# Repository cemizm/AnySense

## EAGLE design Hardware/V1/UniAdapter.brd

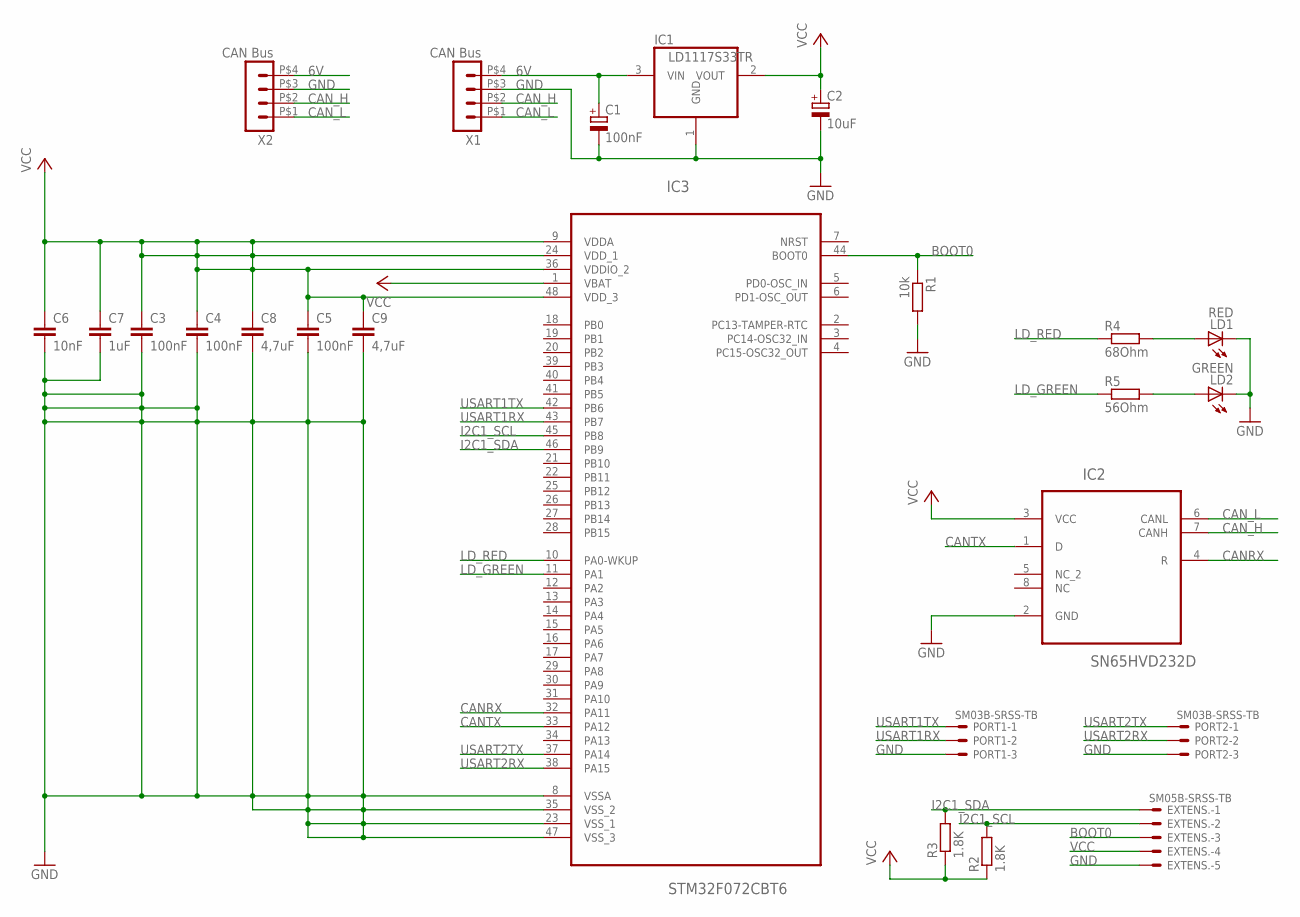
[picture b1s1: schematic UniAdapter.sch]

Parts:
C1: 100nF; CT3216
C2: 10uF; CT3216
C3, C4, C5: 100nF; C0603
C6: 10nF; C0603
C7: 1uF; C0603
C8, C9: 4,7uF; C0603
EXTENS.: SM05B-SRSS-TB
IC1: LD1117S33TR; SOT223
IC2: SN65HVD232D; SOIC127P600X175-8N
IC3: STM32F072CBT6; LQFP48
LD1: RED; CHIPLED_0603
LD2: GREEN; CHIPLED_0603
PORT1, PORT2: SM03B-SRSS-TB
R1: 10k; R0603
R2, R3: 1.8K; R0603
R4: 68Ohm; R0603
R5: 56Ohm; R0603
X1, X2: CAN Bus; 43650-0412

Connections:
6V: C1.+, IC1.3 (VIN), X1.P$4 (4), X2.P$4 (4)
BOOT0: EXTENS..3, IC3.44 (BOOT0), R1.1
CANRX: IC2.4 (R), IC3.32 (PA11)
CANTX: IC2.1 (D), IC3.33 (PA12)
CAN_H: IC2.7 (CANH), X1.P$2 (2), X2.P$2 (2)
CAN_L: IC2.6 (CANL), X1.P$1 (1), X2.P$1 (1)
GND: C1.-, C2.-, C3.2, C4.2, C5.2, C6.2, C7.2, C8.2, C9.2, EXTENS..5, IC1.1 (GND), IC2.2 (GND), IC3.8 (VSSA), IC3.23 (VSS_1), IC3.35 (VSS_2), IC3.47 (VSS_3), LD1.C, LD2.C, PORT1.3, PORT2.3, R1.2, X1.P$3 (3), X2.P$3 (3)
I2C1_SCL: EXTENS..2, IC3.45 (PB8), R2.2
I2C1_SDA: EXTENS..1, IC3.46 (PB9), R3.2
LD_GREEN: IC3.11 (PA1), R5.1
LD_RED: IC3.10 (PA0-WKUP), R4.1
unnamed: LD1.A, R4.2
unnamed: LD2.A, R5.2
USART1RX: IC3.43 (PB7), PORT1.2
USART1TX: IC3.42 (PB6), PORT1.1
USART2RX: IC3.38 (PA15), PORT2.2
USART2TX: IC3.37 (PA14), PORT2.1
VCC: C2.+, C3.1, C4.1, C5.1, C6.1, C7.1, C8.1, C9.1, EXTENS..4, IC1.2 (VOUT), IC2.3 (VCC), IC3.1 (VBAT), IC3.9 (VDDA), IC3.24 (VDD_1), IC3.36 (VDDIO_2), IC3.48 (VDD_3), R2.1, R3.1

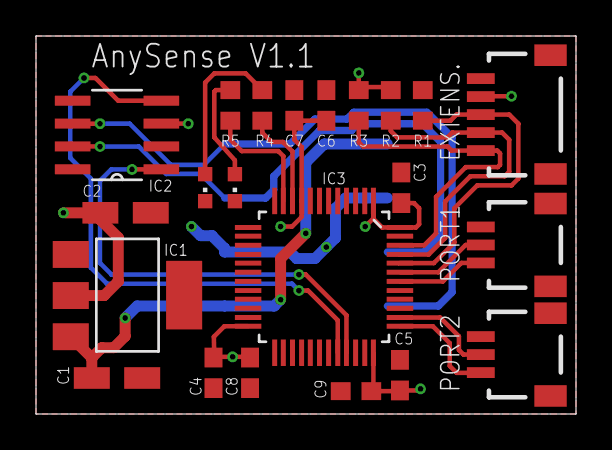
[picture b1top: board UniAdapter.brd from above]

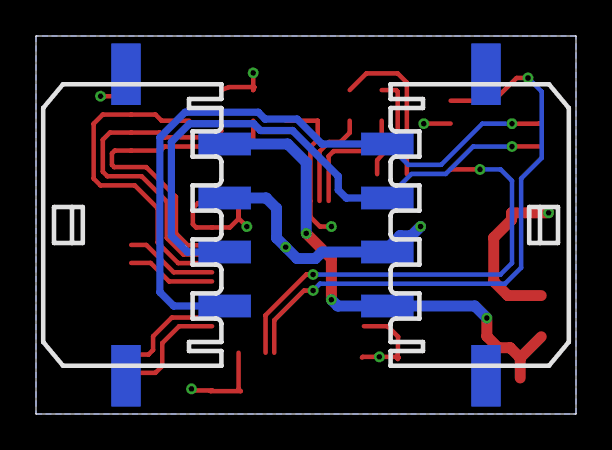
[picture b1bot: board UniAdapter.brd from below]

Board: 2 copper layers, 30.0 x 21.0 mm, 24 parts (2 on the bottom side), 18 nets.

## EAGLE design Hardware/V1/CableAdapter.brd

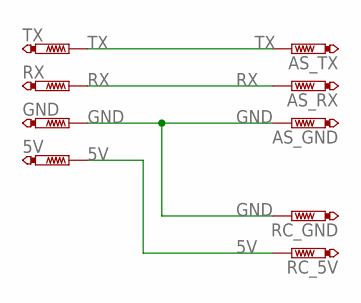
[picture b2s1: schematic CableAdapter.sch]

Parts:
5V: PTR1TP20SQ; TP20SQ
AS_GND: PTR1TP20SQ; TP20SQ
AS_RX: PTR1TP20SQ; TP20SQ
AS_TX: PTR1TP20SQ; TP20SQ
GND: PTR1TP20SQ; TP20SQ
RC_5V: PTR1TP20SQ; TP20SQ
RC_GND: PTR1TP20SQ; TP20SQ
RX: PTR1TP20SQ; TP20SQ
TX: PTR1TP20SQ; TP20SQ

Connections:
5V: 5V.TP, RC_5V.TP
GND: AS_GND.TP, GND.TP, RC_GND.TP
RX: AS_RX.TP, RX.TP
TX: AS_TX.TP, TX.TP

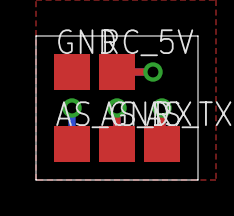
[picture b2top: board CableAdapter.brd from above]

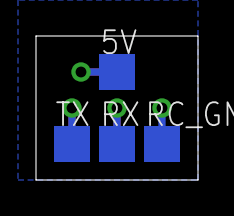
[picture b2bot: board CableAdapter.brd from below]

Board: 2 copper layers, 9.0 x 8.0 mm, 9 parts (4 on the bottom side), 4 nets.

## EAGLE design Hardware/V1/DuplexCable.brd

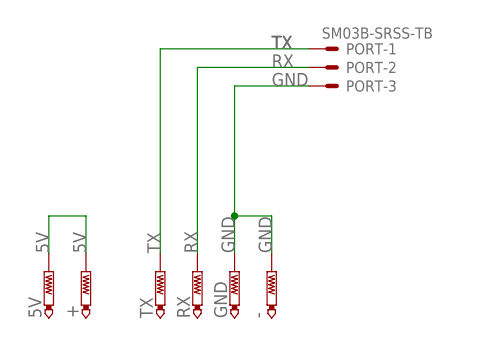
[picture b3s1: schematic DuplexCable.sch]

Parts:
5V: PTR1PAD1-13; P1-13
+: PTR1PAD1-13; P1-13
-: PTR1PAD1-13; P1-13
GND: PTR1PAD1-13; P1-13
PORT: SM03B-SRSS-TB
RX: PTR1PAD1-13; P1-13
TX: PTR1PAD1-13; P1-13

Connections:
5V: 5V.TP, +.TP
GND: -.TP, GND.TP, PORT.3
RX: PORT.2, RX.TP
TX: PORT.1, TX.TP

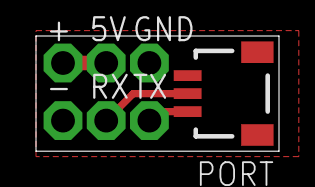
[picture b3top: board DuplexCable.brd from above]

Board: 2 copper layers, 13.5 x 6.4 mm, 7 parts (0 on the bottom side), 4 nets.

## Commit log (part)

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2014-08-21 Initial Hardware Commit
2014-08-21 Firmware Project created
2014-08-24 SPort implemented
2014-08-27 SimpleTelemetry, Naza implemented (unstable)
2014-08-28 Bestückungsdruck angepasst
2014-08-28 Remove unused includes, Naza stable
2014-08-29 Added CoOS to Project
2014-09-03 Major changes, CoOs, Configuration Interface, EEPROM Emulation, S.Port Values
2014-09-04 Added reboot into boot loader memory
2014-09-05 BugFix Throttle, MainForm size
2014-09-05 optimize module & configuration manager
2014-09-05 increase max queues
2014-09-05 Buildnumber increased, release assembly included
2014-09-07 Changed uart mapping for DevKit
2014-09-07 Create binary instead of intel hex (Release configuration)
2014-09-15 added time calculation macro
2014-09-15 return altitude depending on home altitude
2014-09-28 Save changes to config immediately
2014-09-28 Bugfix: Memory Hard fault
2014-10-10 Disco Fixes
2014-10-10 BugFix: HoTT Configuration
2014-10-10 Release package Version 0.9.2
2014-10-11 BugFix: Heading
2014-10-11 Version 0.9.3
2014-10-12 BugFix: S.Port corrupted values at startup
2014-10-13 BugFix max sensor values
2014-10-26 [HW] UniAdapter 1.1
2014-10-28 AnySense 1.1
2014-10-28 Revert "AnySense 1.1"
    This reverts commit 53d5508880b3b2ed964bc1ff9d3bc3f9eadd301f.
2014-11-02 BugFix: Home Direction (HoTT)
2014-11-05 Knot instead of km/h (S.Port), filtering speed value by building average of last 3 values
2014-11-12 Order Codes changed, cream frame reduced, BOOT0 rerouted
2014-11-26 Some enhancements for Graupner relationship
    - HoTT as default for Port 1
    - Selectable source for Flight Direction
    - Selectable source for Variometer
    - Default warn tones for distance and voltage
    - inversion of GPS Position on GPS Screen while NAZA has no Home Position
2014-11-26 Some ideas for adapter cables
2014-11-26 Homepage Content
    Former-commit-id: 758018ecf175f45867fa8f869d2b438da4ce1a04
2014-11-28 Project Clean after Mac Port
    Former-commit-id: a51f8d7b43c891290ce1ad8531b48021fb3c67c0
2014-12-12 Dokumentation überarbeitet
    Former-commit-id: eb7b931f40a4f09fb93cbe6ce75d4c15f046a2a2
2014-12-24 Dokumentation Bilder etc..
    Former-commit-id: f578a4e6b6b732aec2ed08bbe22f1a61f28c0d6d
2014-12-25 UI updates
    Former-commit-id: 9fdede6d122a58dee943c09d1db8466f43948b9e [formerly b1c7611490214108adf8d80db328e3ca83f38c91]
    Former-commit-id: 7a19eff1d16770435108323b8935b12fee48b468
2014-12-25 Stick-Configuration
    Former-commit-id: eab694a87636ecb203a399b5acd5f7ca5952b10a [formerly 6a35c24a26b8ff8181fe9756d8450f8c68a332a6]
    Former-commit-id: 701a58855d858e40705cf02f14d01aac250ffe25
2014-12-28 Stick Configuration changed to FlightMode
    Former-commit-id: deecfa0416f8673ced16468a8acbd2d279d0ce44 [formerly a6082ede0f167e6f04ec9806a9a2a6533bd4eca8]
    Former-commit-id: a8ad13b867792da78b5a1d50d369168541a7c9ed
2014-12-30 Version 0.10.1 – Stick Konfiguration und FrSky/HoTT Telemetrie Support
    Former-commit-id: 2b3e778cad8d112327d2d220ba920d3930ee2c5d [formerly f20541e1cf90ed16b6ad85506f559a6b1edf926f]
    Former-commit-id: f8579eaf5964852471f2219adc3e5acc05f358de
2014-12-30 Stick Konfiguration Dokumentation
    Former-commit-id: b59633202d0c4573de45e93452b9dd35934a8342 [formerly ba22c248138f0436511d1da31eaae2f3355eb004]
    Former-commit-id: 7641de7ee6666b775a8140dbbeb6fee9f903c2bb
2015-01-01 BugFIx: Cells
    Former-commit-id: 697f045f1f4bff6fe8853d658e0b2f12591908d8 [formerly c3e98354df4e487b333de03c0f2fd6e597a73b0b]
    Former-commit-id: 9f81b94029d309eb4cc253e11712f0a3369501bd
2015-01-03 Smart Battery support (unstable)
    Former-commit-id: 2a670e08a0df1234f80090851620fe08525f528a [formerly eb5695c729cc41237139c08976af7351794cd698]
    Former-commit-id: a9f08d8bf061aeec398424b280942c77db99bdc6
2015-01-03 Release Binaries
    Former-commit-id: fd6197e2adc1f665d06fa801bb7ff948136bbbe5 [formerly 9d3d47274fc259d5061d70f34f7129c894760933]
    Former-commit-id: 386c644a9a21f34b4348e8d644f2f4a797c3a251
2015-01-03 BugFix: Current
    Former-commit-id: 9fc99c4f73deff24ee5623f327935bd18c88aa9e [formerly 667b3e5c33ba4a7716b279f2efa3c23faae79ed8]
    Former-commit-id: 37631f0ba0395436d083b426da0b554c79beee58
2015-01-05 Ui enhancements
    Former-commit-id: a23d39751773884d29f5fec33396727da4b3d36f [formerly 9137f2b4c13cfb494da354e4ff67458a2c918ac3]
    Former-commit-id: 79e07315fc51b64a9f0cacf46f41939dd6c32453
2015-01-07 Filter CAN Bus packets by DJI Id
    Former-commit-id: 54452949100020936cdbaba58579f558a87bd81d [formerly f85b9dc0d5949834bd2ff838ef2744404a7e4f7e]
    Former-commit-id: aac698f40edd0ba29f5e4f5d29c40ddb81b9cc72
2015-01-07 lipo percentage is now using frsly lipo sensor if installed instead of calculated lipo voltage
    Former-commit-id: 27ec3ff7227925f7972f2085bfb78bbf1af07cb7 [formerly a7dc16681b51d01886e5f70f33fd513b60e651ca]
    Former-commit-id: 23ff5c5ce7004ce1ca7a1250d55e92fb843e9723
2015-01-10 Documentation extended
    Former-commit-id: b77cab129cca085cd1abde491588992e71643026 [formerly 12172a5565d7ad098706cf33425d1d81977abde7]
    Former-commit-id: fe88c7e5882e5937732630e5215a17561d85f32c
2015-01-17 Added support Wookong M (stable)
    Former-commit-id: f06828dfee2777fee4a6fdb3a236aa6fbab86f04 [formerly f597766a6b13d33cc1c83e729e11365af095e7b8]
    Former-commit-id: ef18e089d1fdfddc5091ef3970844ee1b9335bbe
2015-01-17 Documentation Wiring Wookong
    Former-commit-id: 197824ad49c3068df5e055958c870279c6a635d4 [formerly d2836e593fc53b2a8b18e4839417f5bfa74c7622]
    Former-commit-id: bf5c113b788cb2a16f35ce5a1410f5466b816466
2015-01-26 New Pictures
    Former-commit-id: 47a44493aa367ff845340a8d33272712d4bd6c54 [formerly b9a9c48af1338256687005a043a59400d095d852]
    Former-commit-id: 0e2e1b2f31ec2376011b71324d85b3fb0348abbe
2015-01-30 Smart.Battery Capacity+Percentage
    Former-commit-id: d188dc6bcba09c937c7d68cd26336d819aaab999 [formerly de2045e5214a0bb7af5a829128dd0509d9335e0c]
    Former-commit-id: 2ab8f3aeefd802d34076576775c570ac79f89705
2015-01-30 Konfiguration Manager UI enhancements
    Serial Port Name
    Serial Port automatic reload on connect/disconnect USB device
    ComboBox Enum shows Description Attribute
    Some Enum descriptions extend (more self explaining)
    Former-commit-id: 7bc058fd0141a326d0a89e5537d486f260d6d160 [formerly fb8291af724c23be425bb2e19935fbdac0a1c760]
    Former-commit-id: bd4ba136ccd0201f1a96cb8a31a671d0d662cfab
2015-01-30 Use Smart.Battery percentage and capacity
    Former-commit-id: ba3f78824245907c36abec6bc70ffa163ebd49ed [formerly dd50f614ccb0cf1aaaa320d18f90b2fa90e28f61]
    Former-commit-id: c2ec2170a598aa0f5635f1de8e2383438153587f
2015-01-31 Capacity calculation, lowest cell and percentage calculation optimized
    Former-commit-id: d353cfcbc9f318e47bfd443f16e66ec8f051863b [formerly bcba6c7f75354ffea0ee21e972e7dbcdc504344c]
    Former-commit-id: 652bd6646ec29a6dcd5208aecc18416769d2d79d
2015-01-31 Release Binaries
    Former-commit-id: 470536b0d22c668d79d6bbdfa2c3303ba3d7e725 [formerly c5b2c4a5f653d6a2b0ff39da210c202458f0d4f4]
    Former-commit-id: fa856161ccbe9aa4a3afaa78838b95d298a77ba8
2015-02-06 BugFix: Inverted Altitude (Futaba)
    Former-commit-id: 2059fd52bd5bf7cab668013b147a6946deb4e1d1 [formerly 0306c43ccb7b31aff65e175a829a46c1a103a28e]
    Former-commit-id: 91b9458b7e9f73746d8a9b3c1fb986d58b9049f2
2015-02-06 Bugfix: SerialPort extended name resolve
    Former-commit-id: 4361a9025b0a1b726ebadfbbbba22b9a6fff901f [formerly 45561188780977276c485696d79351465b859f97]
    Former-commit-id: d011d11aebd6d6cf9e2d3f1e184538670f90d77f
2015-02-06 Release Binaries 0.10.7
    Former-commit-id: bd27e9085aefc91d13ec56c4dc03caaca6863f42 [formerly 14af7c058c0c9a696d784edab364a44c068f5286]
    Former-commit-id: 6881f02882009342512a92192cedb89c6dc3f4ac
2015-02-06 Release Binaries 0.10.8
    Former-commit-id: 290420700bdfd546037367020fde73a0c1b0e075 [formerly 969ac0cbf1f0bc106068a8b62137a1346fbfad90]
    Former-commit-id: 15ca9926c056b737e1965d424ef2f5c709619979
2015-02-09 Bugfix Serial Port name
    Former-commit-id: b1374f8d7ec0099b54f9a3af1e2ccc78ccf2a679 [formerly e6cc06d2b245c1c9e1be07a80223621d22653abd]
    Former-commit-id: 445389928537f2ab398de3f074ad1c3b84ad08cc
2015-02-12 Documentation updated
    Former-commit-id: afca945fe484a4f3ee9e61ab719be1cf57472b0e [formerly ab2db8cf39b863b3aa760aeb0a12419e92a8e7cb]
    Former-commit-id: 227b0ee15d8296fbf6bb7962189da6c284c02aee
2015-02-17 improved tilt compensated compass
    Former-commit-id: 26191a5f267c187e8049ca58d0144cb303f65f60 [formerly 93e2894760be93aeb335f8dbd1a75b4cebc6b32a]
    Former-commit-id: 0d21b175cf39b0e02a06e1ea632021cef203066f
2015-02-17 Documentation
    Former-commit-id: f92b99a91328c18869ef95f8cd85f86972db449d [formerly 2ccddfabe4220d405c2fc83008c531d4a9559edf]
    Former-commit-id: 37e4d31b1e852d1d3209ed5f5fecf7a220f7ba47
2015-02-17 NVIC Priorities Changed
    Former-commit-id: b608410933c8e38437bc5d1f40a0e7d213364484 [formerly e0ee831d97667b53efdcf957427389e113cd25a0]
    Former-commit-id: 4064fc5f5552a14db80f172e3df16dc7c1a04113
2015-02-25 Jeti Telemetry (stable)
    Former-commit-id: a72ecf30ff6e28503555687d0a3bbbc72f21dbee [formerly 8aaefdcdd0c19f1582457b1e27d9396e023f7bc4]
    Former-commit-id: de738ad54a98fa7b31d8924231aa73db74f9119c
2015-02-25 Channel stats removed
    Former-commit-id: f4a0e8ed81551a51e206c020887b54a79c817ceb [formerly f81d606912cfac01d909ed1743369fa2f0b8106f]
    Former-commit-id: 383d48b158f79448567fdfa0118dce7f19d3405d
2015-02-27 Flight time Measurement
    Former-commit-id: 5a17160b32ede53cf632c0c1dd38540fbf96c727 [formerly 74f7100d7e745f205fda456f9adaa22ed4a709ee]
    Former-commit-id: 513d921f14da2ac3cf943d2c8f47e7514d536773
2015-02-28 FrSky sensor polling optimized
    Former-commit-id: 0e82c172306a1777b7330ce0e16367614fbb002a [formerly a2f598e73adce91ec8462c36c0114c2cc708abe3]
    Former-commit-id: a6419430900076657c140392e0239dc305ed234d
2015-03-01 Jeti Documentation Updated
    Former-commit-id: 0009b407fe5c108cef8b39f6d0e9bd82b09d484d [formerly cb00897bea03dc84e334311a670c2525afcbdcd4]
    Former-commit-id: 8bf40f4448164ed8854bb67d2d7a9fdcc504aa84
2015-03-06 Dokumentation
    Former-commit-id: bf1a41556a2cb16f28254f4bb356078d7ebefcc7 [formerly 122f18b4cd4f4b83a408d82764e6c2afda368753]
    Former-commit-id: 4598d4fba64a58a80881378a77fcdc9bb534ede5
2015-03-31 Dokumentation / Bedienungsanleitung
    Former-commit-id: 89fbdabe3e94e19e6c7c36ec49690fcb3721537b [formerly 4467c842c1b4fbd81b3837935be9bfb4eb1b28de]
    Former-commit-id: 424c2a8e1f860151bcf00d65f1f7a68c8d771c9d
2015-04-01 FrSky Mapping cleanup + Hide Version Number of Configuration
    Former-commit-id: a6d4f1fc3dd01e0a4b09a7dff612f377d6a981dc [formerly ffec3cc8634efe8e649b1e0d3b5325f539d0dd2f]
    Former-commit-id: 970812a4a8078986968dc6251ddaf41a4eacb437
2015-04-08 FrSky -> HoTT RPM added
    Former-commit-id: a4d75a6a5dc64261534be35c981082d13d76f0ca [formerly 70e5b46bdc65db57c76b1407d0f43d5495d503aa]
    Former-commit-id: e6f649ead8241592fc6b624251b0c3ad24ae369e
2015-04-13 Google Merchant Exporter, use short description for export
    Former-commit-id: cf9ce328ac4e76c54429b87ea4227e776e8f69f7 [formerly d097dc5286380b6177cb570a1f9e3d4e8bf9e45b]
    Former-commit-id: 623161ba80ef9a3f0c7de15063eaffeebd8e4148
2015-05-06 AnySense V1.1 Leiterplatten + Bestückung #3
    Former-commit-id: 593c198c1198a31f97735a0c2702df568af2acf4 [formerly 7c8a19fef4572171d0b0d0c65cc4b21942410e0d]
    Former-commit-id: a2659756fd29e9a2a560bf5236180ee15208b76f
2015-05-09 FrSky S.Port combined values
2015-05-09 Neue Gerber Files
2015-05-09 Homepage Versandkosten Tabelle
2015-05-09 Eigenes Lua Script
2015-05-11 Stencil Gerber
2015-06-18 Lua script developer name
2015-06-18 Calculations
2015-06-18 added some files to ignore
2015-06-28 LUA Script: some optimizations
2015-08-06 Release 1.1.3
2015-08-16 project file fix: jeti private header file included
2015-08-16 Homepage
2015-08-16 Dokumentation Spektrum
2015-08-19 FIX broken options
2015-08-20 Multiplex support
2015-08-20 Release 1.3.01
2015-08-28 Shared Debug Configuration
